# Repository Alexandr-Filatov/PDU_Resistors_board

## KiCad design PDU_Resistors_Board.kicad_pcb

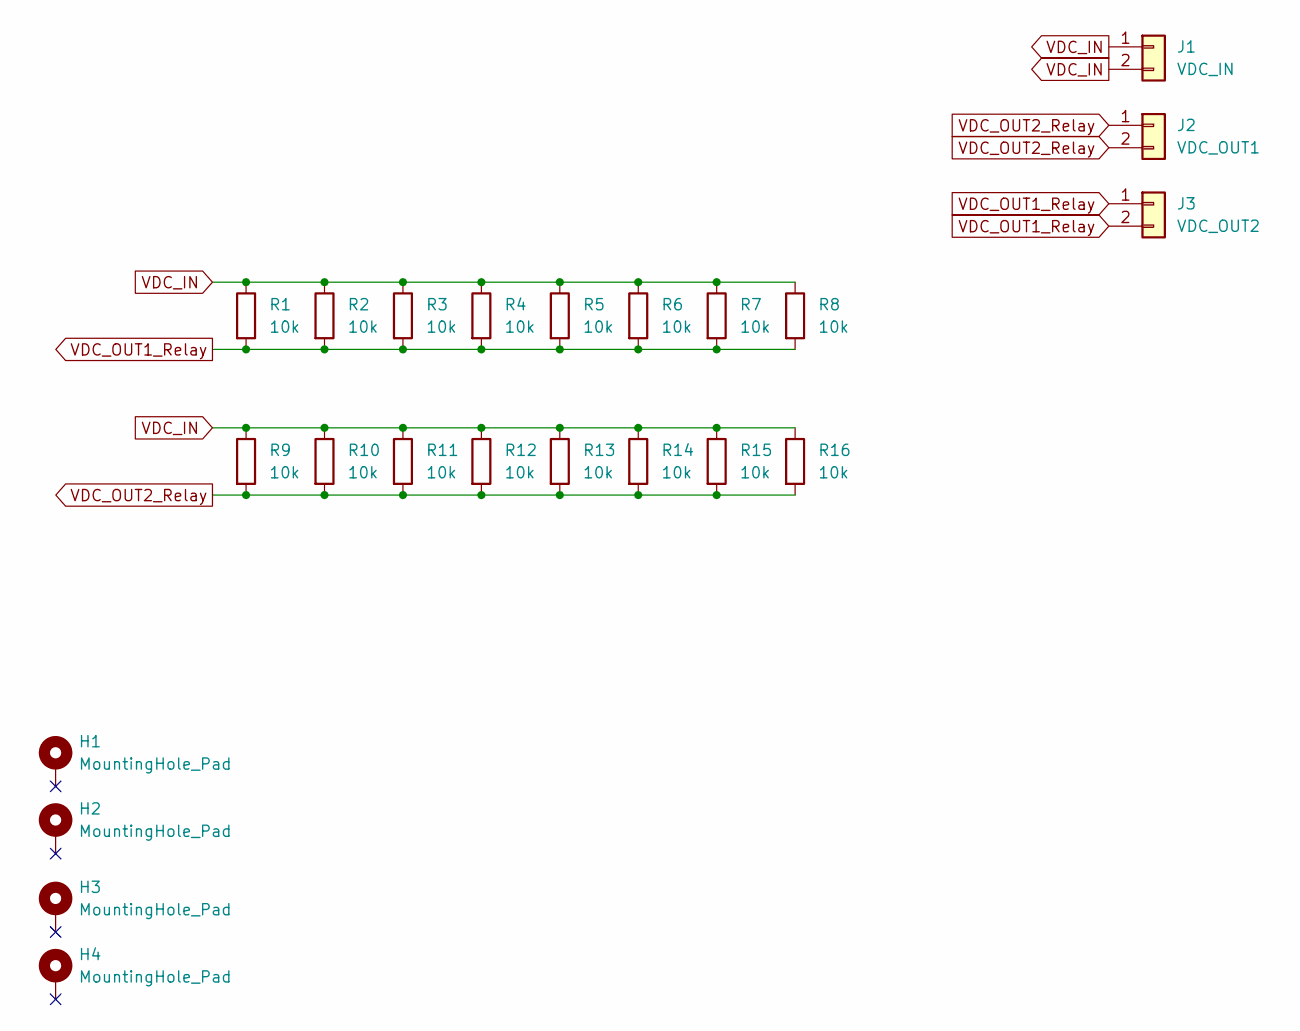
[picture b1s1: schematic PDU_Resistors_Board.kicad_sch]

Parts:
H1, H2, H3, H4: MountingHole_Pad; MountingHole_4.3mm_M4
J1: VDC_IN; Molex_Mini-Fit_Jr_5566-02A_2x01_P4.20mm_Vertical
J2: VDC_OUT1; Molex_Mini-Fit_Jr_5566-02A_2x01_P4.20mm_Vertical
J3: VDC_OUT2; Molex_Mini-Fit_Jr_5566-02A_2x01_P4.20mm_Vertical
R1, R2, R3, R4, R5, R6, R7, R8, R9, R10, R11, R12, R13, R14, R15, R16: 10k; R_Axial_Power_L60.0mm_W14.0mm_P66.04mm

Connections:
VDC_IN: J1.1, J1.2, R1.1, R2.1, R3.1, R4.1, R5.1, R6.1, R7.1, R8.1, R9.1, R10.1, R11.1, R12.1, R13.1, R14.1, R15.1, R16.1
VDC_OUT1_Relay: J3.1, J3.2, R1.2, R2.2, R3.2, R4.2, R5.2, R6.2, R7.2, R8.2
VDC_OUT2_Relay: J2.1, J2.2, R9.2, R10.2, R11.2, R12.2, R13.2, R14.2, R15.2, R16.2

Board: 2 copper layers, 23 parts (8 on the bottom side), 3 nets, no tracks yet.

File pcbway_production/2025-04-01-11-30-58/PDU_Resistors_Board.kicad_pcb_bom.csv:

Designator,Quantity,Value,Footprint,Package,MPN,DNP,Mount_Type,Description
J1,1,VDC_IN,Molex_Mini-Fit_Jr_5566-02A_2x01_P4.20mm_Vertical,,,,tht,"Generic connector, single row, 01x02, script generated (kicad-library-utils/schlib/autogen/connector/)"
J2,1,VDC_OUT1,Molex_Mini-Fit_Jr_5566-02A_2x01_P4.20mm_Vertical,,,,tht,"Generic connector, single row, 01x02, script generated (kicad-library-utils/schlib/autogen/connector/)"
J3,1,VDC_OUT2,Molex_Mini-Fit_Jr_5566-02A_2x01_P4.20mm_Vertical,,,,tht,"Generic connector, single row, 01x02, script generated (kicad-library-utils/schlib/autogen/connector/)"
"R1, R10, R11, R12, R13, R14, R15, R16, R2, R3, R4, R5, R6, R7, R8, R9",16,10k,R_Axial_Power_L60.0mm_W14.0mm_P66.04mm,,,,tht,Resistor

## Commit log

2025-03-24 zero commit
2025-04-01 VER1.0: отправил в резонит на проверку
2025-05-21 VER1.0: длбавил схему в доки
2025-06-18 VER1.0: добавил схему по госту в доки
2025-06-19 VER1.0: добавил сборочный чертеж в доки
2025-06-19 VER1.0: добавил спецификацию в доки
2025-06-20 VER1.0: изменил спецификацию и рамку у СБ
2025-07-01 VER1.0: исправил сборочный и Э3
2025-07-04 VER1.0: исправил СБ
2025-07-09 VER1.0: изменил вес линий в СБ
2025-07-10 VER1.0: исправил Э3
2025-07-15 VER1.0: переделал спецификацию в автокаде
